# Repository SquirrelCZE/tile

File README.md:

# Tile

Tile is a generic mounting system designed for small robots. 
It is a specification of dimensions of one mount position with positions of four screws.
The idea is that one can attach anything to said position, from 3D printed parts to PCBs.

This gives as abillity to easily reuse parts and rebuild the robot in different configuration easily, same way one could expect from LEGO.
The key difference is that it is more sturdy (as screws are used) and it is easy to make compatible PCB.

We intentially designed the tile to allow mounting of parts on thin wall from both sides.
This is achieved by shifting the holes in a way, that when the shape is flipped, the holes won't collide (even when one uses nuts to screw something in place)

The position is shaped like square with beveled corners, this makes it possible to form a grid of mount positions. 
Bigger parts can overlap multiple tiles, it is up to designed to decided whenever that is sensible choice.
Corners are beveled to create a spot between positions on grid for wires.

Given that we use this for 3D printing, the models expect nuts to be inserted in the models to get proper screw thread.

The most used configuration T24 is 24x24mm square with four positions for M2 screws.

The tile is used in our robot Koke heavily https://schpin.org/robots/koke.html and we allready benefited from this on another robot that just reused a lot of the parts.

## Repository content

The main truth for the tile is it's SCAD library - `tile.scad`.
The rest of the repository is as follows:

 * **dxf/** contains dxf shapes for some grid layous that can be directly imported to other CADs made with SCAD. Note that SCAD approximates circles with n-gon.	
 * **example/** simple examples of tile shapes that can be used
 * **extra/** contains more complex models using tile, such as holder for raspberry or 90degree bracket.
 * **pcb/** PCBs used for our robot designed in KiCAD that are Tile compatible.

## Gallery

### Examples

Simple square with T24 mount on both sides:

### Koke

This is an example of more complex assembly: part of Koke's leg.
You can see that the parts are connected with tiles (such as the tip of the leg) and that there are multiple tile mount spots.

### PCBs

There are two PCBs that are in production stage (that is they may be improved in time but there is little motivation to do so). 
Both are designed in KiCAD and we buy them in bulk.

The first one is small 4-layer power distribution board for use with our servomotors.
The power is brought in usually via the XT30 connector space and we have multiple of these on the robot itself.
We have custom footprint for servoconnectors that is compatible with servomotor connectors with 2.54/2mm spacing with pins in following configuration: S|VCC|GND. 
The idea is that servomotors are connected to free servo connectors and one is left to connect the S| |GND pair to the controller (that is, without the VCC line).

Second board is just really simple holder for two housings for 18650 batteries, that are pararelly connected. 
There are no connectros to be used, rather we expect the wires to be soldered directly on the board itself.

### Prototype PCBs

We have a prototype of board with STM32G4 processor that can be powered from PDB board above.
The board is designed to control our servomotors or to be attached to same communication bus.

The v1 prototype worked (as we could write code for it and blink a LED), but it misses logic level shifter for the servo bus which makes it not really usable.

The v2 fixes that and even adds IMU, however we should switch to smaller package for the processor to fit all on one side of the PCB and we can't do that now given chip shortage, so v2 is delayed until we can do that.

## Drawings of T24

All dimensions are in `mm`.

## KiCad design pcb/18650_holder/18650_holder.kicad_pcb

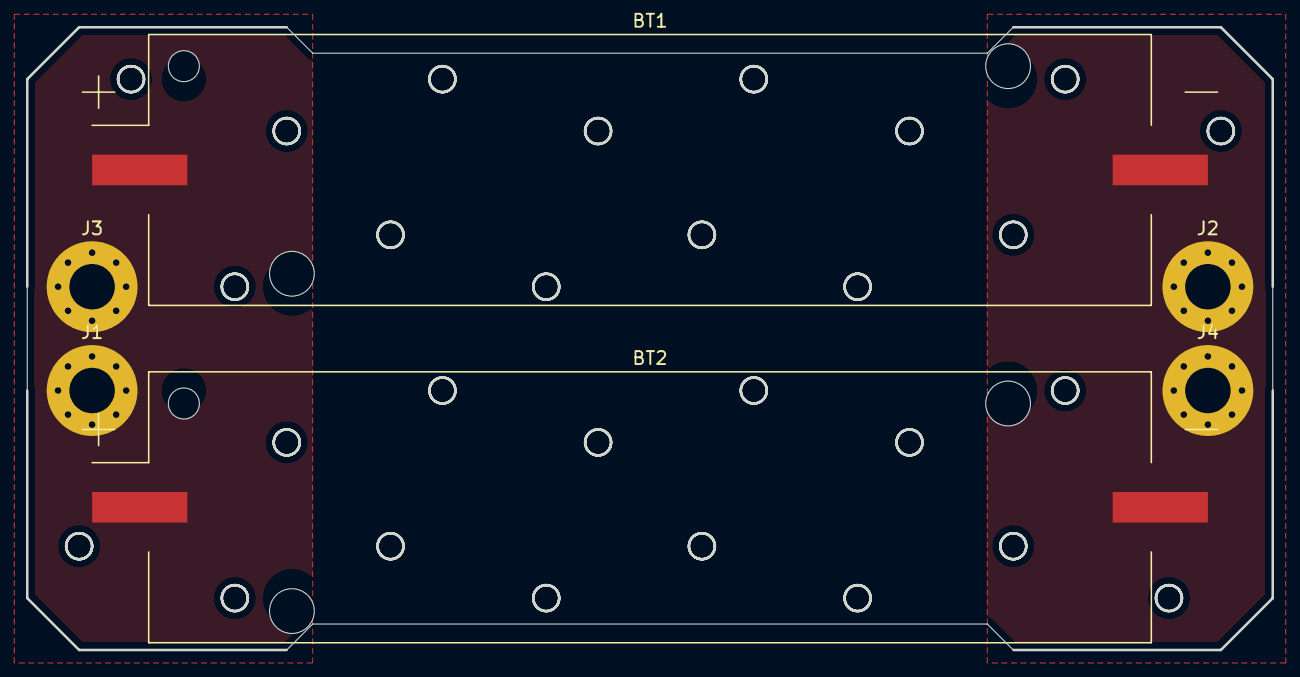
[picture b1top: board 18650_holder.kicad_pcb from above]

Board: 2 copper layers, 96.0 x 48.0 mm, 6 parts (0 on the bottom side), 2 nets, no tracks yet.

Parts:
BT1, BT2: Battery_Cell; 18650_holder
J1, J2, J3, J4: Conn_01x01_Male; MountingHole_3.5mm_Pad_Via

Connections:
GND: BT1.2, BT2.2, J2.1, J4.1
VCC: BT1.1, BT2.1, J1.1, J3.1

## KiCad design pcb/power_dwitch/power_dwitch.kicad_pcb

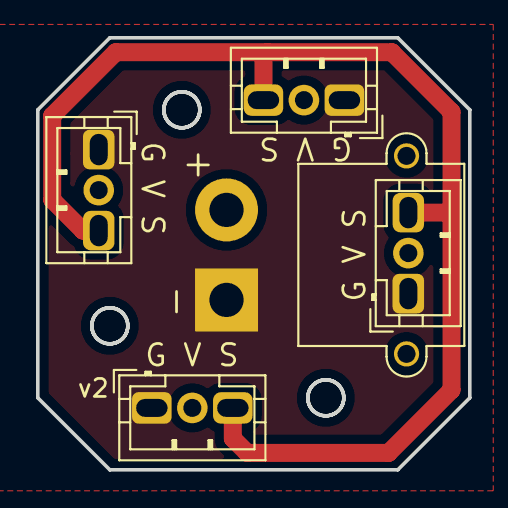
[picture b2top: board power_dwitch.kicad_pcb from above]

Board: 4 copper layers, 24.0 x 24.0 mm, 5 parts (0 on the bottom side), 3 nets.

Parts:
J1, J2, J3, J4: Conn_01x03_Male; JST_PH_B3B-PH-K_1x03_P2.00mm_Vertical
J5: Conn_01x02_Male; AMASS_XT30PW-M_1x02_P2.50mm_Horizontal

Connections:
GND: J1.1, J2.1, J3.1, J4.1, J5.1
S: J1.3, J2.3, J3.3, J4.3
VCC: J1.2, J2.2, J3.2, J4.2, J5.2

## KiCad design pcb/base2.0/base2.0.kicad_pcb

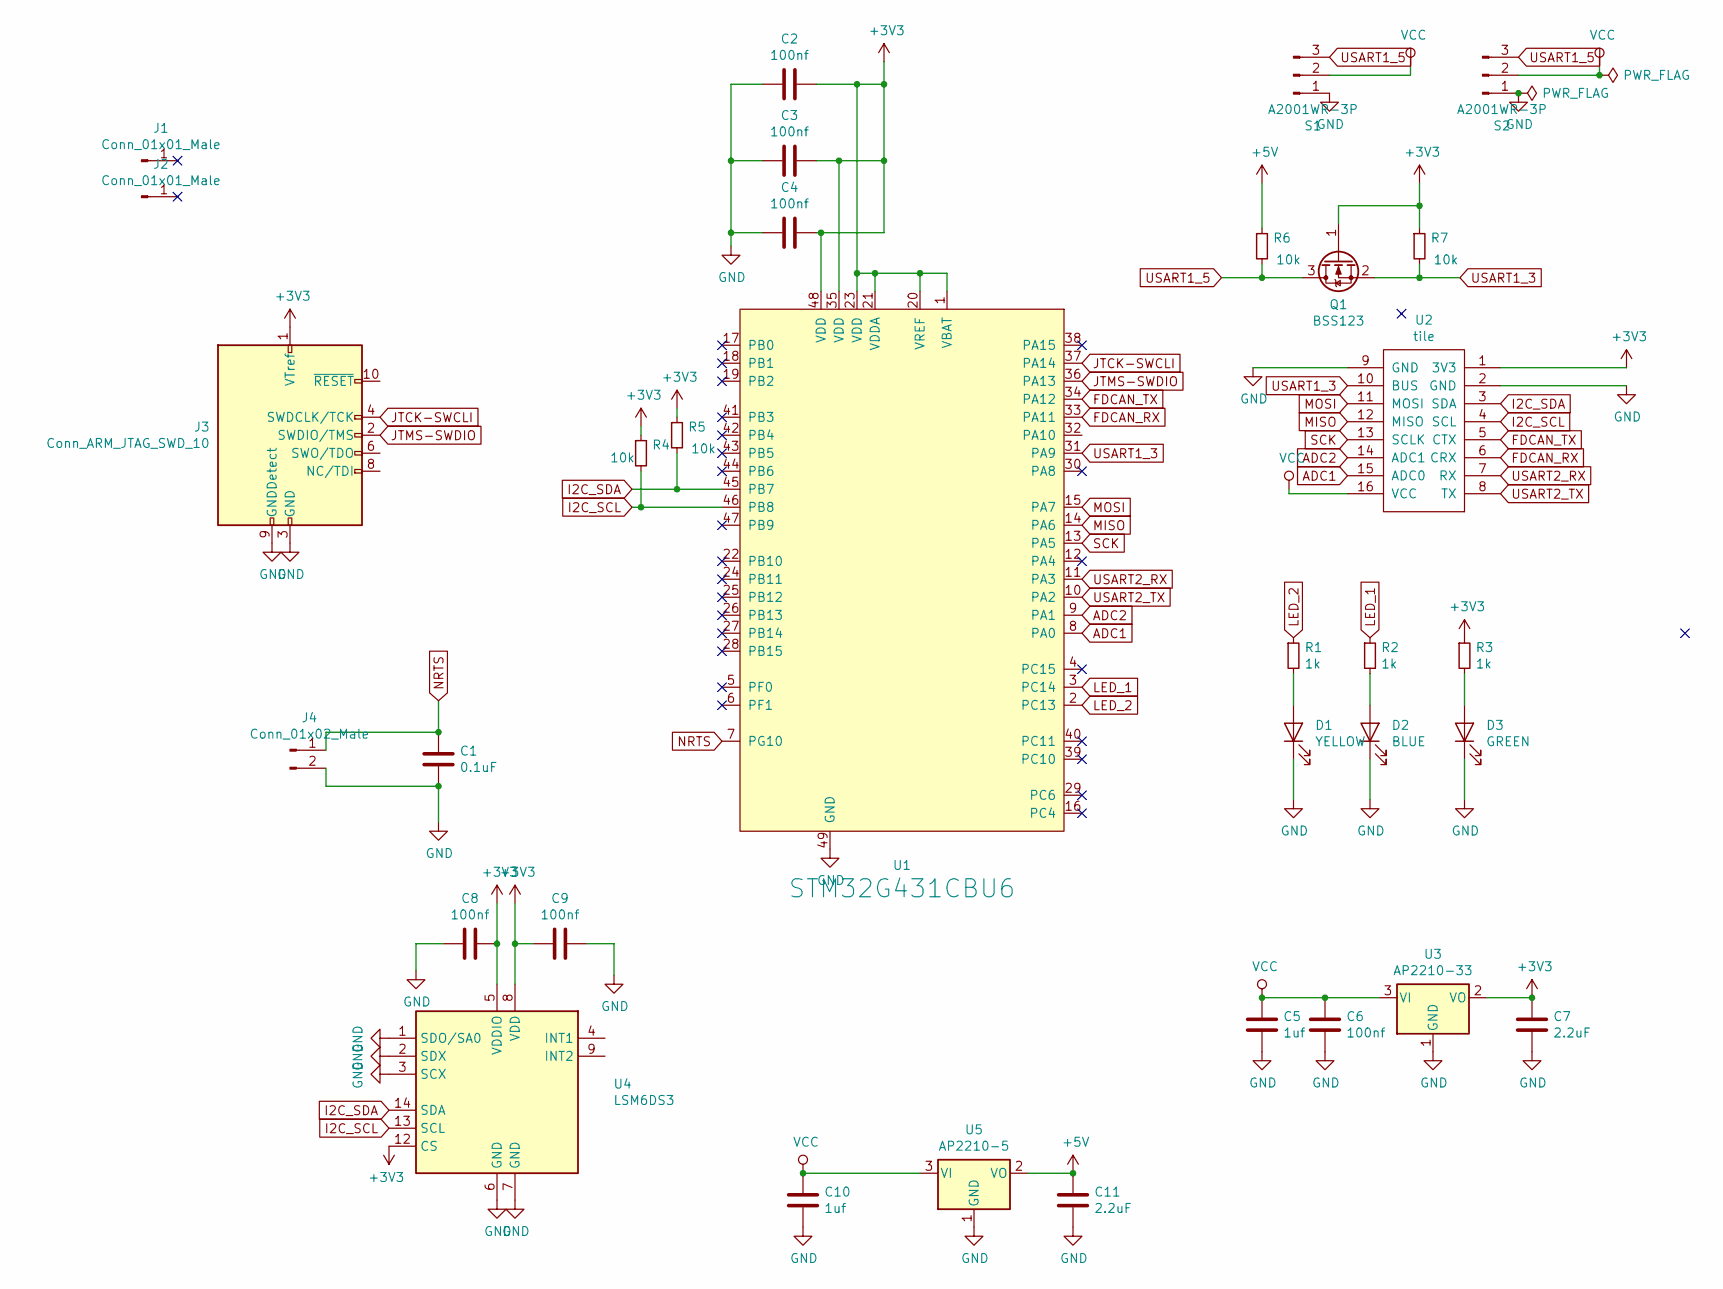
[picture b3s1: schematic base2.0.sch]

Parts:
C1: 0.1uF; C_0402_1005Metric; LCSC C1525
C2, C3, C4, C6, C8, C9: 100nf; C_0402_1005Metric; LCSC C1525
C5, C10: 1uf; C_0402_1005Metric; LCSC C52923
C7, C11: 2.2uF; C_0402_1005Metric; LCSC C12530
D1: YELLOW; LED_0603_1608Metric; LCSC C72038
D2: BLUE; LED_0603_1608Metric; LCSC C72041
D3: GREEN; LED_0603_1608Metric; LCSC C72043
J1, J2: Conn_01x01_Male; MountingHole_2.2mm_M2_DIN965_Pad
J3: Conn_ARM_JTAG_SWD_10; PinHeader_2x05_P1.27mm_Vertical
J4: Conn_01x02_Male; PinHeader_1x02_P1.27mm_Vertical
Q1: BSS123; SOT-23
R1, R2, R3: 1k; R_0402_1005Metric; LCSC C11702
R4, R5, R6, R7: 10k; R_0402_1005Metric; LCSC C25744
S1, S2: A2001WR-3P; jst_bus_horizontal
U1: STM32G431CBU6; QFN-48-1EP_7x7mm_P0.5mm_EP5.6x5.6mm; LCSC C529356
U2: tile
U3: AP2210-33; SOT-23; LCSC C155508
U4: LSM6DS3; LGA-14_3x2.5mm_P0.5mm_LayoutBorder3x4y
U5: AP2210-5; SOT-23; LCSC C500758

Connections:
+3V3: C2.1, C3.1, C4.1, C7.1, C8.1, C9.2, J3.1 (VTref), Q1.1 (G), R3.1, R4.1, R5.1, R7.1, U1.1 (VBAT), U1.20 (VREF), U1.21 (VDDA), U1.23 (VDD), U1.35 (VDD), U1.48 (VDD), U2.1 (3V3), U3.2 (VO), U4.5 (VDDIO), U4.8 (VDD), U4.12 (CS)
+5V: C11.1, R6.1, U5.2 (VO)
ADC1: U1.8 (PA0), U2.15 (ADC0)
ADC2: U1.9 (PA1), U2.14 (ADC1)
FDCAN_RX: U1.33 (PA11), U2.6 (CRX)
FDCAN_TX: U1.34 (PA12), U2.5 (CTX)
GND: C1.2, C2.2, C3.2, C4.2, C5.2, C6.2, C7.2, C8.2, C9.1, C10.2, C11.2, D1.1 (K), D2.1 (K), D3.1 (K), J3.3 (GND), J3.5 (GND), J3.9 (GNDDetect), J4.2, S1.1, S2.1, U1.49 (GND), U2.2 (GND), U2.9 (GND), U3.1 (GND), U4.1 (SDO/SA0), U4.2 (SDX), U4.3 (SCX), U4.6 (GND), U4.7 (GND), U5.1 (GND)
I2C_SCL: R4.2, U1.46 (PB8), U2.4 (SCL), U4.13 (SCL)
I2C_SDA: R5.2, U1.45 (PB7), U2.3 (SDA), U4.14 (SDA)
JTCK-SWCLI: J3.4 (SWDCLK/TCK), U1.37 (PA14)
JTMS-SWDIO: J3.2 (SWDIO/TMS), U1.36 (PA13)
LED_1: R2.1, U1.3 (PC14)
LED_2: R1.1, U1.2 (PC13)
MISO: U1.14 (PA6), U2.12 (MISO)
MOSI: U1.15 (PA7), U2.11 (MOSI)
NRTS: C1.1, J4.1, U1.7 (PG10)
unnamed: D1.2 (A), R1.2
unnamed: D2.2 (A), R2.2
unnamed: D3.2 (A), R3.2
SCK: U1.13 (PA5), U2.13 (SCLK)
USART1_3: Q1.2 (S), R7.2, U1.31 (PA9), U2.10 (BUS)
USART1_5: Q1.3 (D), R6.2, S1.3, S2.3
USART2_RX: U1.11 (PA3), U2.7 (RX)
USART2_TX: U1.10 (PA2), U2.8 (TX)
VCC: C5.1, C6.1, C10.1, S1.2, S2.2, U2.16 (VCC), U3.3 (VI), U5.3 (VI)

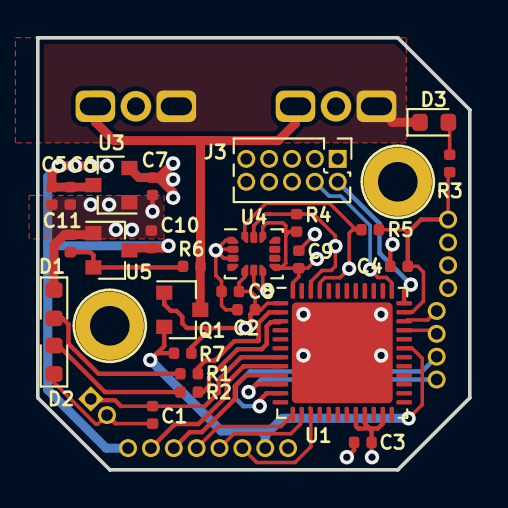
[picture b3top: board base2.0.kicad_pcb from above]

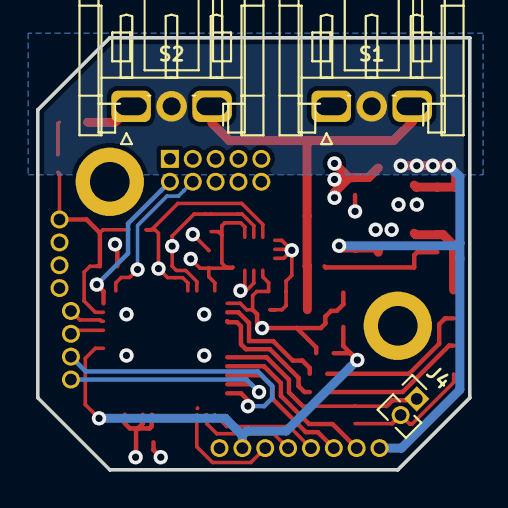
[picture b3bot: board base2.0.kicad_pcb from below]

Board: 4 copper layers, 24.0 x 24.0 mm, 33 parts (3 on the bottom side), 25 nets.

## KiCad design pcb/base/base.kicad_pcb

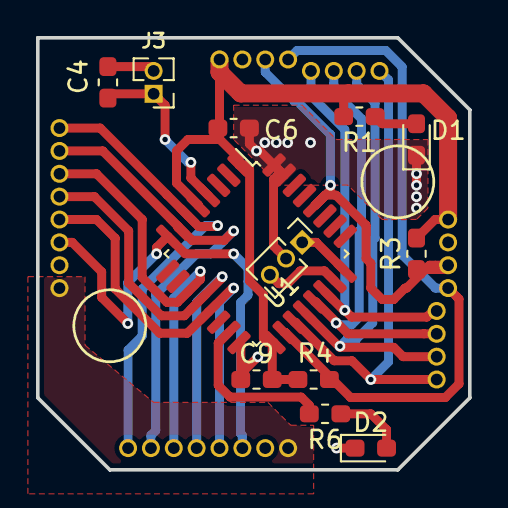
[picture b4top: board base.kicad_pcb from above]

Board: 2 copper layers, 24.0 x 24.0 mm, 13 parts (0 on the bottom side), 20 nets.

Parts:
C4, C6, C9: 100nf; C_0603_1608Metric_Pad1.05x0.95mm_HandSolder
D1, D2: LED; LED_0603_1608Metric_Pad1.05x0.95mm_HandSolder
J3: Conn_01x02_Male; PinHeader_1x02_P1.27mm_Vertical
J4: Conn_01x03_Male; PinHeader_1x03_P1.27mm_Vertical
R1, R6: R_Small; R_0603_1608Metric_Pad1.05x0.95mm_HandSolder
R3, R4: 4k7; R_0603_1608Metric_Pad1.05x0.95mm_HandSolder
U1: STM32G431KBT6; LQFP-32_7x7mm_P0.8mm
U3: tile

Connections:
+3V3: C6.2, C9.2, R1.2, R3.2, R4.2, U1.1, U1.5, U1.17, U3.1
ADC0: U1.6, U3.16
ADC1: U1.7, U3.15
BUS: U1.8, U3.11
CRX: U1.21, U3.6
CTX: U1.22, U3.5
GND: C4.1, C6.1, C9.1, D1.1, D2.1, J3.2, J4.2, U1.16, U1.31, U1.32, U3.2, U3.10
I2C_CLK: R4.1, U1.18, U3.4
I2C_SDA: R3.1, U1.28, U3.3
LED: R6.2, U1.15
unnamed: C4.2, J3.1, U1.4
unnamed: D1.2, R1.1
unnamed: D2.2, R6.1
SPI_CLK: U1.11, U3.14
SPI_MISO: U1.12, U3.13
SPI_MOSI: U1.13, U3.12
SWDCLK: J4.1, U1.24
SWDIO: J4.3, U1.23
USART1_RX: U1.20, U3.7
USART1_TX: U1.19, U3.8

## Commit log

2019-04-04 vanilla
2020-01-04 wololo
2020-01-04 added tile.scad examples
2020-01-04 updated tile_H example
2020-01-04 added sandwitch example
2020-01-04 fixes to example imageS
2020-01-04 added automatic example readme
2020-01-04 fixed readme target for examples
2020-01-04 fixed rendering resolution and added shape png
2020-01-04 fixed intro readme, bad img syntax
2020-12-11 added puncholes dxf
2021-01-30 cleaning/upgrades got collection of little modes over sime time, added dxf"
2021-01-30 changed img sizes
2021-01-30 Fixed image size
2021-01-30 slightly better description
2021-01-30 updated readme and pics
2021-01-30 fixed holes orientation
2021-01-30 fixed tile_H
2021-01-31 fixed typo
2021-02-05 added scad
2021-02-19 fixed errors in scheme
2021-02-19 fixed includes
2021-07-14 le update
2021-09-10 Small changes to base pcb
2021-09-10 fixed i2c lines on base2.0 pcb
2021-11-21 removed base output files
2021-12-08 added another pcbs
2021-12-08 added pics of pcbs
2021-12-08 added pics of pcbs to readme
2021-12-08 added pic of tile in example
2021-12-09 Added small pic
2021-12-09 changed the way example readme works
2021-12-09 Added more description of pictures
2021-12-09 Modified sandwitch example
2021-12-09 added femur
2021-12-09 Added default params, clips and increase M2 nut size
2021-12-09 regenerated examples
